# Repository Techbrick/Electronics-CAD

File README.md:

# Welcome!
This is a simple directory containing sources and STL files for 3D Printable parts.  Mostly, the files in this directory are aimed at helping the Electronics team.

## License
Files are licensed CC-BY-NC.  Basically, feel free to remix, just make sure to properly mark where you got them, and don't use them for commercial purposes.

# Lifecam HD-3000 Mount
These files are for rigidly mounting a Microsoft Lifecam HD-3000 USB camera to your robot frame.  

## Heatsink for high power LEDs:
The current plan is to try a 1" long section of [Heatsink USA's 1.813" heatsink](http://www.heatsinkusa.com/1-813/) for the LED star.  
Drill and Tap four #8-32 screw holes, centered on the corners of a 23/16" x 1/2" rectangle, on the face of the heatsink. 

Secure the LED star to the heatsink with thermal tape.

Mount standard 20mm optics over the LEDs. 

## Wiring for high power LEDs:
Currently planning to use [Meanwell Constant Current](http://www.ledsupply.com/led-drivers/mean-well-ldb-l-series-cc-buck-boost-mode) regulators.  Power in will be connected to the PDP, and the enable signal will be tied into a Rio DIO, so that we can control the LEDs being on or off.

(Note:  For any high power LED, please make sure you can turn it off if you are not using it.  Your teammates, opponents, field staff, and spectators will all appreciate it.)

# LED Rings:
the 60,80,100, and 120 rings are based on the specs here:
https://www.superbrightleds.com/moreinfo/led-headlight-accent-lights/led-halo-angel-eye-headlight-accent-lights/49/#/tab/Specifications

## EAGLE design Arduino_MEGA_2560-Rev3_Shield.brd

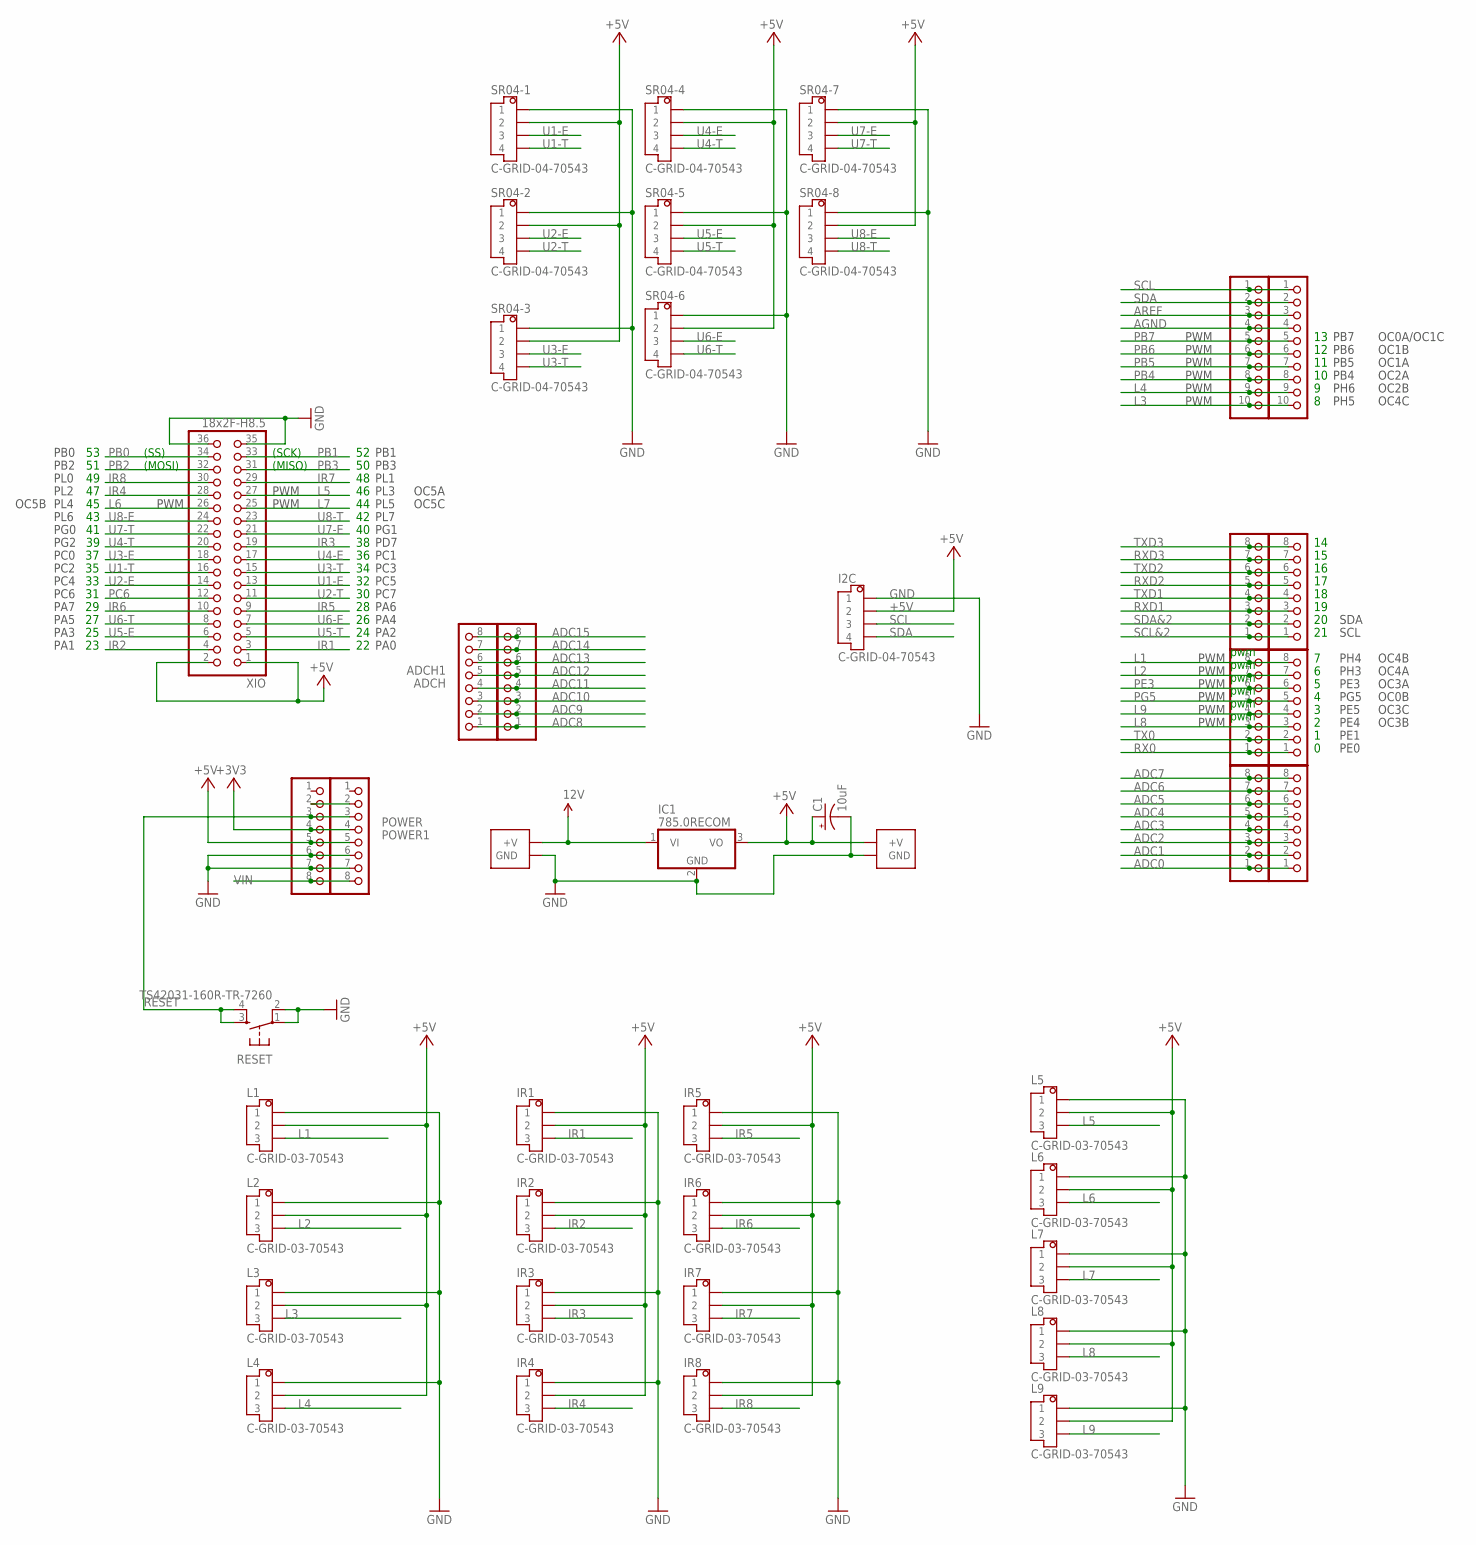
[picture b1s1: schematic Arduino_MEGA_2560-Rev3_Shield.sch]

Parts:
ADCH, ADCH1: 8x1F-H8.5; 1X08
ADCL, ADCL1: 8x1F-H8.5; 1X08
C1: 10uF; CT6032
COMMUNICATION, COMMUNICATION1: 8x1F-H8.5; 1X08
I2C: C-GRID-04-70543; 70543-04
IC1: 785.0RECOM; RECOM-78E
IR1, IR2, IR3, IR4, IR5, IR6, IR7, IR8: C-GRID-03-70543; 70543-03
JP1, JP6: 10x1F-H8.5; 1X10
L1, L2, L3, L4, L5, L6, L7, L8, L9: C-GRID-03-70543; 70543-03
POWER, POWER1: 8x1F-H8.5; 1X08
PWML, PWML1: 8x1F-H8.5; 1X08
RESET: TS42031-160R-TR-7260; TACTILE-PTH
SR04-1, SR04-2, SR04-3, SR04-4, SR04-5, SR04-6, SR04-7, SR04-8: C-GRID-04-70543; 70543-04
U$1, U$2: POWERIN; 1825640000
XIO: 18x2F-H8.5; 2X18

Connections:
12V: IC1.1 (VI), U$1.B1 (+V), U$1.B2 (+V)
+3V3: POWER.4, POWER1.4
+5V: C1.+, I2C.2, IC1.3 (VO), IR1.2, IR2.2, IR3.2, IR4.2, IR5.2, IR6.2, IR7.2, IR8.2, L1.2, L2.2, L3.2, L4.2, L5.2, L6.2, L7.2, L8.2, L9.2, POWER.5, POWER1.5, SR04-1.2, SR04-2.2, SR04-3.2, SR04-4.2, SR04-5.2, SR04-6.2, SR04-7.2, SR04-8.2, U$2.B1 (+V), U$2.B2 (+V), XIO.1, XIO.2
ADC0: ADCL.1, ADCL1.1
ADC1: ADCL.2, ADCL1.2
ADC2: ADCL.3, ADCL1.3
ADC3: ADCL.4, ADCL1.4
ADC4: ADCL.5, ADCL1.5
ADC5: ADCL.6, ADCL1.6
ADC6: ADCL.7, ADCL1.7
ADC7: ADCL.8, ADCL1.8
ADC8: ADCH.1, ADCH1.1
ADC9: ADCH.2, ADCH1.2
ADC10: ADCH.3, ADCH1.3
ADC11: ADCH.4, ADCH1.4
ADC12: ADCH.5, ADCH1.5
ADC13: ADCH.6, ADCH1.6
ADC14: ADCH.7, ADCH1.7
ADC15: ADCH.8, ADCH1.8
AGND: JP1.4, JP6.4
AREF: JP1.3, JP6.3
GND: C1.-, I2C.1, IC1.2 (GND), IR1.1, IR2.1, IR3.1, IR4.1, IR5.1, IR6.1, IR7.1, IR8.1, L1.1, L2.1, L3.1, L4.1, L5.1, L6.1, L7.1, L8.1, L9.1, POWER.6, POWER.7, POWER1.6, POWER1.7, RESET.1, RESET.2, SR04-1.1, SR04-2.1, SR04-3.1, SR04-4.1, SR04-5.1, SR04-6.1, SR04-7.1, SR04-8.1, U$1.A1 (GND), U$1.A2 (GND), U$2.A1 (GND), U$2.A2 (GND), XIO.35, XIO.36
IR1: IR1.3, XIO.3
IR2: IR2.3, XIO.4
IR3: IR3.3, XIO.19
IR4: IR4.3, XIO.28
IR5: IR5.3, XIO.9
IR6: IR6.3, XIO.10
IR7: IR7.3, XIO.29
IR8: IR8.3, XIO.30
L1: L1.3, PWML.8, PWML1.8
L2: L2.3, PWML.7, PWML1.7
L3: JP1.10, JP6.10, L3.3
L4: JP1.9, JP6.9, L4.3
L5: L5.3, XIO.27
L6: L6.3, XIO.26
L7: L7.3, XIO.25
L8: L8.3, PWML.3, PWML1.3
L9: L9.3, PWML.4, PWML1.4
unnamed: POWER.2, POWER1.2
PB0: XIO.34
PB1: XIO.33
PB2: XIO.32
PB3: XIO.31
PB4: JP1.8, JP6.8
PB5: JP1.7, JP6.7
PB6: JP1.6, JP6.6
PB7: JP1.5, JP6.5
PC6: XIO.12
PE3: PWML.6, PWML1.6
PG5: PWML.5, PWML1.5
RESET: POWER.3, POWER1.3, RESET.3, RESET.4
RX0: PWML.1, PWML1.1
RXD1: COMMUNICATION.3, COMMUNICATION1.3
RXD2: COMMUNICATION.5, COMMUNICATION1.5
RXD3: COMMUNICATION.7, COMMUNICATION1.7
SCL: I2C.3, JP1.1, JP6.1
SCL&2: COMMUNICATION.1, COMMUNICATION1.1
SDA: I2C.4, JP1.2, JP6.2
SDA&2: COMMUNICATION.2, COMMUNICATION1.2
TX0: PWML.2, PWML1.2
TXD1: COMMUNICATION.4, COMMUNICATION1.4
TXD2: COMMUNICATION.6, COMMUNICATION1.6
TXD3: COMMUNICATION.8, COMMUNICATION1.8
U1-E: SR04-1.3, XIO.13
U1-T: SR04-1.4, XIO.16
U2-E: SR04-2.3, XIO.14
U2-T: SR04-2.4, XIO.11
U3-E: SR04-3.3, XIO.18
U3-T: SR04-3.4, XIO.15
U4-E: SR04-4.3, XIO.17
U4-T: SR04-4.4, XIO.20
U5-E: SR04-5.3, XIO.6
U5-T: SR04-5.4, XIO.5
U6-E: SR04-6.3, XIO.7
U6-T: SR04-6.4, XIO.8
U7-E: SR04-7.3, XIO.21
U7-T: SR04-7.4, XIO.22
U8-E: SR04-8.3, XIO.24
U8-T: SR04-8.4, XIO.23
VIN: POWER.8, POWER1.8

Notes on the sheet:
pwm
(SS)
(MOSI)
(SCK)
(MISO)
PWM
PL5
PL3
PB1
PB3
PL1
PL7
PG1
PD7
PC1
PC3
PC5
PC7
PA6
PA4
PA2
PA0
PB0
PB2
PL0
PL2
PL4
PL6
PG0
PG2
PC0
PC2
PC4
PC6
PA7
PA5
PA3
PA1
PB7
PB6

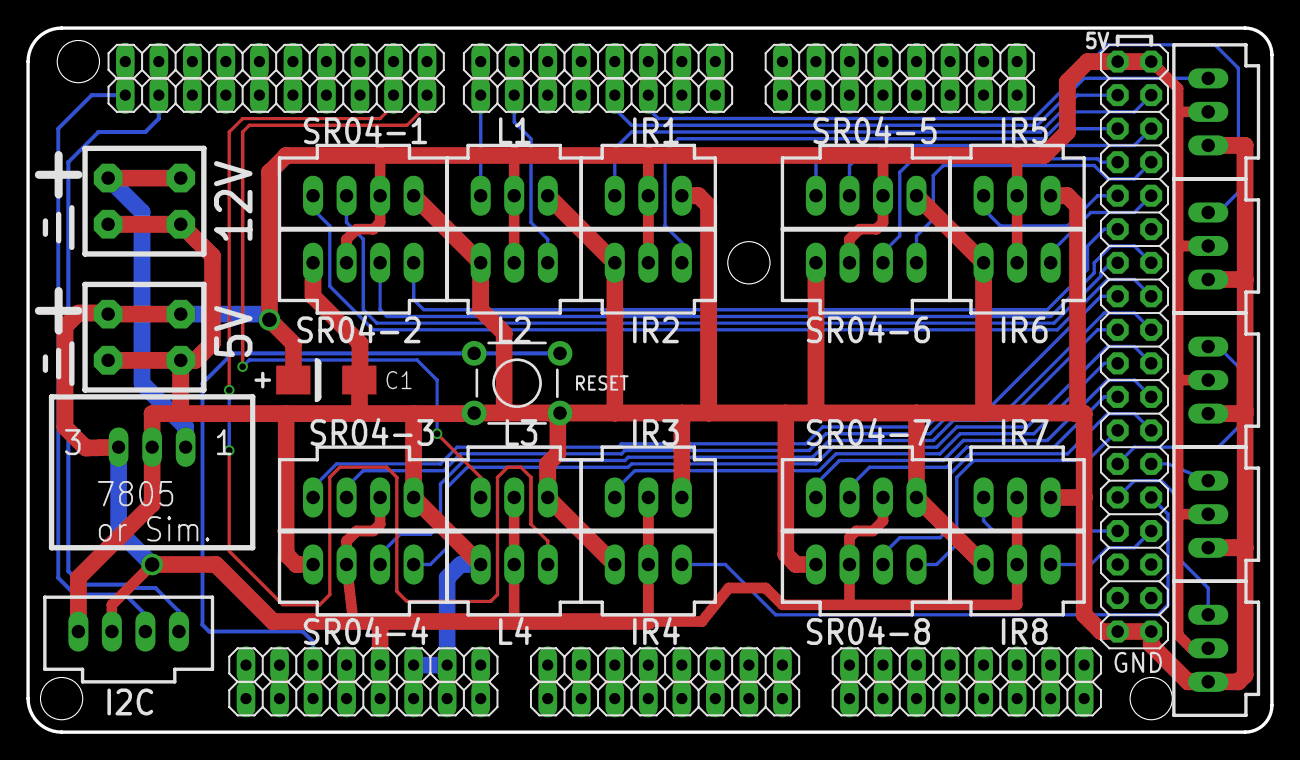
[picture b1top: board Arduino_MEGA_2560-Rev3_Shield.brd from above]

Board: 2 copper layers, 94.2 x 53.3 mm, 44 parts (0 on the bottom side), 76 nets.

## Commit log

2017-01-15 adding readme
2017-01-15 forgot the lifecam scad file!
2017-01-15 and forgot the source stl...
2017-01-15 shouldn't have been there
2017-01-15 update to readme
2017-01-15 adding superbrighled rings
2017-01-15 small update
2017-01-16 initial height didn't work, correcting
2017-01-16 added tabs to push the nuts
2017-01-28 Adding files for new gear design
2017-01-28 tweaking gear cover
2017-02-15 new housing for gear sensors
2017-02-23 changed the 60mm led ring to fit actual dimensions
2018-01-13 Synching real boards with git repo

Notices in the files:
parts and their libraries:
SparkFun-Retired: Licensing:Creative Commons ShareAlike 4.0 International - https://creativecommons.org/licenses/by-sa/4.0
